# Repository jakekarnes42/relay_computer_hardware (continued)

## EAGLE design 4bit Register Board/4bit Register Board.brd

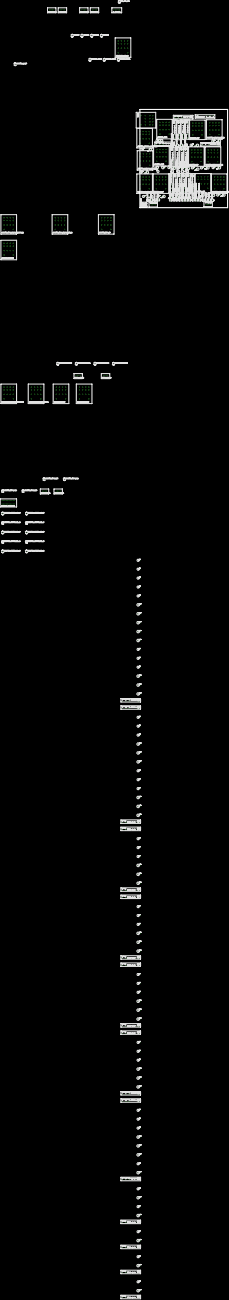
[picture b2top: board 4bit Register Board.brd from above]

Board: 2 copper layers, 125.0 x 140.0 mm, 237 parts (0 on the bottom side), 134 nets, no tracks yet.

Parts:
CCR:D3, CCR:D5, CCR:D7, CCR:D9, CCR:D11, CCR:D13: 1N4007; RAD2,5
CCR:D4, CCR:D6, CCR:D8, CCR:D10, CCR:D12, CCR:D14: 1N5359VERT_SML; RAD2.5_D2
CCR:ENABLE_DATA:D1: 1N4007; RAD2,5
CCR:ENABLE_DATA:D2: 1N5359VERT_SML; RAD2.5_D2
CCR:ENABLE_DATA:K1: PY14-02
CCR:K2: HF41F-12-Z
CCR:K3: PY14-02
CCR:K4, CCR:K5, CCR:K6, CCR:K7: HF41F-12-H
CCR:LED0, CCR:LED1, CCR:LED2, CCR:LED3: LED3MM
CCR_CONTROL:X1: 55932-0530
INPUT_ADDR:X1: 55932-0430
INPUT_AU_CCR:X1: 55932-0430
INPUT_AU_DATA:X1: 55932-0430
INPUT_DATA:X1: 55932-0430
INPUT_LU_CCR:X1: 55932-0430
INPUT_LU_DATA:X1: 55932-0430
LED_ADDR0, LED_ADDR1, LED_ADDR2, LED_ADDR3: LED3MM
LED_DATA0, LED_DATA1, LED_DATA2, LED_DATA3: LED3MM
LED_LOAD_CCR: LED3MM
OUTPUT_AU_TMP1:X1, OUTPUT_AU_TMP2:X1: 55932-0430
OUTPUT_LU_TMP1:X1, OUTPUT_LU_TMP2:X1: 55932-0430
PWR_BLK:PWR: PWR_BLK; 1751248
REGISTER_A:D3, REGISTER_A:D5, REGISTER_A:D7, REGISTER_A:D9, REGISTER_A:D11, REGISTER_A:D13, REGISTER_A:D17, REGISTER_A:D19: 1N4007; RAD2,5
REGISTER_A:D4, REGISTER_A:D6, REGISTER_A:D8, REGISTER_A:D10, REGISTER_A:D12, REGISTER_A:D14, REGISTER_A:D18, REGISTER_A:D20: 1N5359VERT_SML; RAD2.5_D2
REGISTER_A:ENABLE_ADDRESS:D1: 1N4007; RAD2,5
REGISTER_A:ENABLE_ADDRESS:D2: 1N5359VERT_SML; RAD2.5_D2
REGISTER_A:ENABLE_ADDRESS:K1: PY14-02
REGISTER_A:ENABLE_DATA:D1: 1N4007; RAD2,5
REGISTER_A:ENABLE_DATA:D2: 1N5359VERT_SML; RAD2.5_D2
REGISTER_A:ENABLE_DATA:K1: PY14-02
REGISTER_A:K2, REGISTER_A:K9: HF41F-12-Z
REGISTER_A:K3, REGISTER_A:K10: PY14-02
REGISTER_A:K4, REGISTER_A:K5, REGISTER_A:K6, REGISTER_A:K7: HF41F-12-H
REGISTER_A:LED0, REGISTER_A:LED1, REGISTER_A:LED2, REGISTER_A:LED3: LED3MM
REGISTER_B:D3, REGISTER_B:D5, REGISTER_B:D7, REGISTER_B:D9, REGISTER_B:D11, REGISTER_B:D13, REGISTER_B:D17, REGISTER_B:D19: 1N4007; RAD2,5
REGISTER_B:D4, REGISTER_B:D6, REGISTER_B:D8, REGISTER_B:D10, REGISTER_B:D12, REGISTER_B:D14, REGISTER_B:D18, REGISTER_B:D20: 1N5359VERT_SML; RAD2.5_D2
REGISTER_B:ENABLE_ADDRESS:D1: 1N4007; RAD2,5
REGISTER_B:ENABLE_ADDRESS:D2: 1N5359VERT_SML; RAD2.5_D2
REGISTER_B:ENABLE_ADDRESS:K1: PY14-02
REGISTER_B:ENABLE_DATA:D1: 1N4007; RAD2,5
REGISTER_B:ENABLE_DATA:D2: 1N5359VERT_SML; RAD2.5_D2
REGISTER_B:ENABLE_DATA:K1: PY14-02
REGISTER_B:K2, REGISTER_B:K9: HF41F-12-Z
REGISTER_B:K3, REGISTER_B:K10: PY14-02
REGISTER_B:K4, REGISTER_B:K5, REGISTER_B:K6, REGISTER_B:K7: HF41F-12-H
REGISTER_B:LED0, REGISTER_B:LED1, REGISTER_B:LED2, REGISTER_B:LED3: LED3MM
REGISTER_C:D3, REGISTER_C:D5, REGISTER_C:D7, REGISTER_C:D9, REGISTER_C:D11, REGISTER_C:D13, REGISTER_C:D17, REGISTER_C:D19: 1N4007; RAD2,5
REGISTER_C:D4, REGISTER_C:D6, REGISTER_C:D8, REGISTER_C:D10, REGISTER_C:D12, REGISTER_C:D14, REGISTER_C:D18, REGISTER_C:D20: 1N5359VERT_SML; RAD2.5_D2
REGISTER_C:ENABLE_ADDRESS:D1: 1N4007; RAD2,5
REGISTER_C:ENABLE_ADDRESS:D2: 1N5359VERT_SML; RAD2.5_D2
REGISTER_C:ENABLE_ADDRESS:K1: PY14-02
REGISTER_C:ENABLE_DATA:D1: 1N4007; RAD2,5
REGISTER_C:ENABLE_DATA:D2: 1N5359VERT_SML; RAD2.5_D2
REGISTER_C:ENABLE_DATA:K1: PY14-02
REGISTER_C:K2, REGISTER_C:K9: HF41F-12-Z
REGISTER_C:K3, REGISTER_C:K10: PY14-02
REGISTER_C:K4, REGISTER_C:K5, REGISTER_C:K6, REGISTER_C:K7: HF41F-12-H
REGISTER_C:LED0, REGISTER_C:LED1, REGISTER_C:LED2, REGISTER_C:LED3: LED3MM
REGISTER_CONTROL:LED_1, REGISTER_CONTROL:LED_2, REGISTER_CONTROL:LED_3, REGISTER_CONTROL:LED_4, REGISTER_CONTROL:LED_5, REGISTER_CONTROL:LED_6, REGISTER_CONTROL:LED_7, REGISTER_CONTROL:LED_8, REGISTER_CONTROL:LED_9, REGISTER_CONTROL:LED_10, REGISTER_CONTROL:LED_11, REGISTER_CONTROL:LED_12, REGISTER_CONTROL:LED_13, REGISTER_CONTROL:LED_14, REGISTER_CONTROL:LED_15, REGISTER_CONTROL:LED_16, REGISTER_CONTROL:LED_17, REGISTER_CONTROL:LED_18, REGISTER_CONTROL:LED_19, REGISTER_CONTROL:LED_20: LED3MM
REGISTER_CONTROL:X2: 55917-2030
REGISTER_TMP1:D3, REGISTER_TMP1:D5, REGISTER_TMP1:D7, REGISTER_TMP1:D9, REGISTER_TMP1:D11, REGISTER_TMP1:D13, REGISTER_TMP1:D17, REGISTER_TMP1:D19, REGISTER_TMP1:ENABLE_ADDRESS:D1, REGISTER_TMP1:ENABLE_DATA:D1, REGISTER_TMP2:D3, REGISTER_TMP2:D5, REGISTER_TMP2:D7, REGISTER_TMP2:D9, REGISTER_TMP2:D11, REGISTER_TMP2:D13, REGISTER_TMP2:D17, REGISTER_TMP2:D19, REGISTER_TMP2:ENABLE_ADDRESS:D1, REGISTER_TMP2:ENABLE_DATA:D1: 1N4007; RAD2,5
REGISTER_TMP1:D4, REGISTER_TMP1:D6, REGISTER_TMP1:D8, REGISTER_TMP1:D10, REGISTER_TMP1:D12, REGISTER_TMP1:D14, REGISTER_TMP1:D18, REGISTER_TMP1:D20, REGISTER_TMP1:ENABLE_ADDRESS:D2, REGISTER_TMP1:ENABLE_DATA:D2, REGISTER_TMP2:D4, REGISTER_TMP2:D6, REGISTER_TMP2:D8, REGISTER_TMP2:D10, REGISTER_TMP2:D12, REGISTER_TMP2:D14, REGISTER_TMP2:D18, REGISTER_TMP2:D20, REGISTER_TMP2:ENABLE_ADDRESS:D2, REGISTER_TMP2:ENABLE_DATA:D2: 1N5359VERT_SML; RAD2.5_D2
REGISTER_TMP1:ENABLE_ADDRESS:K1, REGISTER_TMP1:ENABLE_DATA:K1, REGISTER_TMP1:K3, REGISTER_TMP1:K10, REGISTER_TMP2:ENABLE_ADDRESS:K1, REGISTER_TMP2:ENABLE_DATA:K1, REGISTER_TMP2:K3, REGISTER_TMP2:K10: PY14-02
REGISTER_TMP1:K2, REGISTER_TMP1:K9, REGISTER_TMP2:K2, REGISTER_TMP2:K9: HF41F-12-Z
REGISTER_TMP1:K4, REGISTER_TMP1:K5, REGISTER_TMP1:K6, REGISTER_TMP1:K7, REGISTER_TMP2:K4, REGISTER_TMP2:K5, REGISTER_TMP2:K6, REGISTER_TMP2:K7: HF41F-12-H
REGISTER_TMP1:LED0, REGISTER_TMP1:LED1, REGISTER_TMP1:LED2, REGISTER_TMP1:LED3, REGISTER_TMP2:LED0, REGISTER_TMP2:LED1, REGISTER_TMP2:LED2, REGISTER_TMP2:LED3: LED3MM

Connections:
+12V: CCR:K2.4, CCR:K3.31, CCR:K3.41, PWR_BLK:PWR.2, REGISTER_A:K2.4, REGISTER_A:K3.31, REGISTER_A:K3.41, REGISTER_A:K9.4, REGISTER_A:K10.31, REGISTER_A:K10.41, REGISTER_B:K2.4, REGISTER_B:K3.31, REGISTER_B:K3.41, REGISTER_B:K9.4, REGISTER_B:K10.31, REGISTER_B:K10.41, REGISTER_C:K2.4, REGISTER_C:K3.31, REGISTER_C:K3.41, REGISTER_C:K9.4, REGISTER_C:K10.31, REGISTER_C:K10.41, REGISTER_TMP1:K2.4, REGISTER_TMP1:K3.31, REGISTER_TMP1:K3.41, REGISTER_TMP1:K9.4, REGISTER_TMP1:K10.31, REGISTER_TMP1:K10.41, REGISTER_TMP2:K2.4, REGISTER_TMP2:K3.31, REGISTER_TMP2:K3.41, REGISTER_TMP2:K9.4, REGISTER_TMP2:K10.31, REGISTER_TMP2:K10.41
ADDR0: INPUT_ADDR:X1.4, LED_ADDR0.A, REGISTER_A:ENABLE_ADDRESS:K1.14, REGISTER_B:ENABLE_ADDRESS:K1.14, REGISTER_C:ENABLE_ADDRESS:K1.14, REGISTER_TMP1:ENABLE_ADDRESS:K1.14, REGISTER_TMP2:ENABLE_ADDRESS:K1.14
ADDR1: INPUT_ADDR:X1.3, LED_ADDR1.A, REGISTER_A:ENABLE_ADDRESS:K1.24, REGISTER_B:ENABLE_ADDRESS:K1.24, REGISTER_C:ENABLE_ADDRESS:K1.24, REGISTER_TMP1:ENABLE_ADDRESS:K1.24, REGISTER_TMP2:ENABLE_ADDRESS:K1.24
ADDR2: INPUT_ADDR:X1.2, LED_ADDR2.A, REGISTER_A:ENABLE_ADDRESS:K1.34, REGISTER_B:ENABLE_ADDRESS:K1.34, REGISTER_C:ENABLE_ADDRESS:K1.34, REGISTER_TMP1:ENABLE_ADDRESS:K1.34, REGISTER_TMP2:ENABLE_ADDRESS:K1.34
ADDR3: INPUT_ADDR:X1.1, LED_ADDR3.A, REGISTER_A:ENABLE_ADDRESS:K1.44, REGISTER_B:ENABLE_ADDRESS:K1.44, REGISTER_C:ENABLE_ADDRESS:K1.44, REGISTER_TMP1:ENABLE_ADDRESS:K1.44, REGISTER_TMP2:ENABLE_ADDRESS:K1.44
CCR:D$2: CCR:D3.A, CCR:D4.A
CCR:D$3: CCR:D5.A, CCR:D6.A
CCR:D$4: CCR:D7.A, CCR:D8.A
CCR:D$5: CCR:D9.A, CCR:D10.A
CCR:D$6: CCR:D11.A, CCR:D12.A
CCR:D$7: CCR:D13.A, CCR:D14.A
CCR:ENABLE_DATA:D$1: CCR:ENABLE_DATA:D1.A, CCR:ENABLE_DATA:D2.A
CCR:HOLD: CCR:K3.32, CCR:K4.5, CCR:K5.5, CCR:K6.5, CCR:K7.5
CCR:IN: CCR:D3.C, CCR:K2.1, CCR:K3.42
CCR:SELECT: CCR:ENABLE_DATA:D1.C, CCR:ENABLE_DATA:K1.A2, CCR:K2.3
DATA0: INPUT_AU_DATA:X1.4, INPUT_DATA:X1.4, INPUT_LU_DATA:X1.4, LED_DATA0.A, REGISTER_A:ENABLE_DATA:K1.44, REGISTER_B:ENABLE_DATA:K1.44, REGISTER_C:ENABLE_DATA:K1.44, REGISTER_TMP1:ENABLE_DATA:K1.44, REGISTER_TMP2:ENABLE_DATA:K1.44
DATA1: INPUT_AU_DATA:X1.3, INPUT_DATA:X1.3, INPUT_LU_DATA:X1.3, LED_DATA1.A, REGISTER_A:ENABLE_DATA:K1.34, REGISTER_B:ENABLE_DATA:K1.34, REGISTER_C:ENABLE_DATA:K1.34, REGISTER_TMP1:ENABLE_DATA:K1.34, REGISTER_TMP2:ENABLE_DATA:K1.34
DATA2: INPUT_AU_DATA:X1.2, INPUT_DATA:X1.2, INPUT_LU_DATA:X1.2, LED_DATA2.A, REGISTER_A:ENABLE_DATA:K1.24, REGISTER_B:ENABLE_DATA:K1.24, REGISTER_C:ENABLE_DATA:K1.24, REGISTER_TMP1:ENABLE_DATA:K1.24, REGISTER_TMP2:ENABLE_DATA:K1.24
DATA3: INPUT_AU_DATA:X1.1, INPUT_DATA:X1.1, INPUT_LU_DATA:X1.1, LED_DATA3.A, REGISTER_A:ENABLE_DATA:K1.14, REGISTER_B:ENABLE_DATA:K1.14, REGISTER_C:ENABLE_DATA:K1.14, REGISTER_TMP1:ENABLE_DATA:K1.14, REGISTER_TMP2:ENABLE_DATA:K1.14
GND: CCR:D4.C, CCR:D6.C, CCR:D8.C, CCR:D10.C, CCR:D12.C, CCR:D14.C, CCR:ENABLE_DATA:D2.C, CCR:ENABLE_DATA:K1.A1, CCR:K2.2, CCR:K3.A1, CCR:K4.2, CCR:K5.2, CCR:K6.2, CCR:K7.2, CCR:LED0.K, CCR:LED1.K, CCR:LED2.K, CCR:LED3.K, LED_ADDR0.K, LED_ADDR1.K, LED_ADDR2.K, LED_ADDR3.K, LED_DATA0.K, LED_DATA1.K, LED_DATA2.K, LED_DATA3.K, LED_LOAD_CCR.K, PWR_BLK:PWR.1, REGISTER_A:D4.C, REGISTER_A:D6.C, REGISTER_A:D8.C, REGISTER_A:D10.C, REGISTER_A:D12.C, REGISTER_A:D14.C, REGISTER_A:D18.C, REGISTER_A:D20.C, REGISTER_A:ENABLE_ADDRESS:D2.C, REGISTER_A:ENABLE_ADDRESS:K1.A1, REGISTER_A:ENABLE_DATA:D2.C, REGISTER_A:ENABLE_DATA:K1.A1, REGISTER_A:K2.2, REGISTER_A:K3.A1, REGISTER_A:K4.2, REGISTER_A:K5.2, REGISTER_A:K6.2, REGISTER_A:K7.2, REGISTER_A:K9.2, REGISTER_A:K10.A1, REGISTER_A:LED0.K, REGISTER_A:LED1.K, REGISTER_A:LED2.K, REGISTER_A:LED3.K, REGISTER_B:D4.C, REGISTER_B:D6.C, REGISTER_B:D8.C, REGISTER_B:D10.C, REGISTER_B:D12.C, REGISTER_B:D14.C, REGISTER_B:D18.C, REGISTER_B:D20.C, REGISTER_B:ENABLE_ADDRESS:D2.C, REGISTER_B:ENABLE_ADDRESS:K1.A1, REGISTER_B:ENABLE_DATA:D2.C, REGISTER_B:ENABLE_DATA:K1.A1, REGISTER_B:K2.2, REGISTER_B:K3.A1, REGISTER_B:K4.2, REGISTER_B:K5.2, REGISTER_B:K6.2, REGISTER_B:K7.2, REGISTER_B:K9.2, REGISTER_B:K10.A1, REGISTER_B:LED0.K, REGISTER_B:LED1.K, REGISTER_B:LED2.K, REGISTER_B:LED3.K, REGISTER_C:D4.C, REGISTER_C:D6.C, REGISTER_C:D8.C, REGISTER_C:D10.C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
LOADA_A: REGISTER_A:D19.C, REGISTER_A:K10.A2, REGISTER_CONTROL:LED_11.A
LOADA_B: REGISTER_B:D19.C, REGISTER_B:K10.A2, REGISTER_CONTROL:LED_13.A
LOADA_C: REGISTER_C:D19.C, REGISTER_C:K10.A2, REGISTER_CONTROL:LED_15.A
LOADA_TMP1: REGISTER_CONTROL:LED_17.A, REGISTER_TMP1:D19.C, REGISTER_TMP1:K10.A2
LOADA_TMP2: REGISTER_CONTROL:LED_19.A, REGISTER_TMP2:D19.C, REGISTER_TMP2:K10.A2
LOADD_A: REGISTER_A:D5.C, REGISTER_A:K3.A2, REGISTER_CONTROL:LED_1.A, REGISTER_CONTROL:X2.1
LOADD_B: REGISTER_B:D5.C, REGISTER_B:K3.A2, REGISTER_CONTROL:LED_3.A, REGISTER_CONTROL:X2.5
LOADD_C: REGISTER_C:D5.C, REGISTER_C:K3.A2, REGISTER_CONTROL:LED_5.A, REGISTER_CONTROL:X2.9
LOADD_TMP1: REGISTER_CONTROL:LED_7.A, REGISTER_CONTROL:X2.13, REGISTER_TMP1:D5.C, REGISTER_TMP1:K3.A2
LOADD_TMP2: REGISTER_CONTROL:LED_9.A, REGISTER_CONTROL:X2.17, REGISTER_TMP2:D5.C, REGISTER_TMP2:K3.A2
LOAD_CCR: CCR:D5.C, CCR:K3.A2, CCR_CONTROL:X1.1, LED_LOAD_CCR.A
unnamed: OUTPUT_AU_TMP2:X1.1, OUTPUT_LU_TMP2:X1.1, REGISTER_TMP2:D7.C, REGISTER_TMP2:ENABLE_ADDRESS:K1.41, REGISTER_TMP2:ENABLE_DATA:K1.11, REGISTER_TMP2:K4.1, REGISTER_TMP2:K4.4, REGISTER_TMP2:LED3.A
unnamed: OUTPUT_AU_TMP2:X1.2, OUTPUT_LU_TMP2:X1.2, REGISTER_TMP2:D9.C, REGISTER_TMP2:ENABLE_ADDRESS:K1.31, REGISTER_TMP2:ENABLE_DATA:K1.21, REGISTER_TMP2:K5.1, REGISTER_TMP2:K5.4, REGISTER_TMP2:LED2.A
unnamed: OUTPUT_AU_TMP2:X1.3, OUTPUT_LU_TMP2:X1.3, REGISTER_TMP2:D11.C, REGISTER_TMP2:ENABLE_ADDRESS:K1.21, REGISTER_TMP2:ENABLE_DATA:K1.31, REGISTER_TMP2:K6.1, REGISTER_TMP2:K6.4, REGISTER_TMP2:LED1.A
unnamed: OUTPUT_AU_TMP2:X1.4, OUTPUT_LU_TMP2:X1.4, REGISTER_TMP2:D13.C, REGISTER_TMP2:ENABLE_ADDRESS:K1.11, REGISTER_TMP2:ENABLE_DATA:K1.41, REGISTER_TMP2:K7.1, REGISTER_TMP2:K7.4, REGISTER_TMP2:LED0.A
unnamed: REGISTER_B:D7.C, REGISTER_B:ENABLE_ADDRESS:K1.41, REGISTER_B:ENABLE_DATA:K1.11, REGISTER_B:K4.1, REGISTER_B:K4.4, REGISTER_B:LED3.A
unnamed: CCR:ENABLE_DATA:K1.14, INPUT_AU_CCR:X1.4, INPUT_LU_CCR:X1.4
unnamed: CCR:ENABLE_DATA:K1.24, INPUT_AU_CCR:X1.3, INPUT_LU_CCR:X1.3
unnamed: CCR:ENABLE_DATA:K1.34, INPUT_AU_CCR:X1.2, INPUT_LU_CCR:X1.2
unnamed: CCR:ENABLE_DATA:K1.44, INPUT_AU_CCR:X1.1, INPUT_LU_CCR:X1.1
unnamed: CCR:D7.C, CCR:ENABLE_DATA:K1.11, CCR:K4.1, CCR:K4.4, CCR:LED3.A, CCR_CONTROL:X1.2
unnamed: CCR:D9.C, CCR:ENABLE_DATA:K1.21, CCR:K5.1, CCR:K5.4, CCR:LED2.A, CCR_CONTROL:X1.3
unnamed: CCR:D11.C, CCR:ENABLE_DATA:K1.31, CCR:K6.1, CCR:K6.4, CCR:LED1.A, CCR_CONTROL:X1.4
unnamed: CCR:D13.C, CCR:ENABLE_DATA:K1.41, CCR:K7.1, CCR:K7.4, CCR:LED0.A, CCR_CONTROL:X1.5
unnamed: OUTPUT_AU_TMP1:X1.1, OUTPUT_LU_TMP1:X1.1, REGISTER_TMP1:D7.C, REGISTER_TMP1:ENABLE_ADDRESS:K1.41, REGISTER_TMP1:ENABLE_DATA:K1.11, REGISTER_TMP1:K4.1, REGISTER_TMP1:K4.4, REGISTER_TMP1:LED3.A
unnamed: OUTPUT_AU_TMP1:X1.2, OUTPUT_LU_TMP1:X1.2, REGISTER_TMP1:D9.C, REGISTER_TMP1:ENABLE_ADDRESS:K1.31, REGISTER_TMP1:ENABLE_DATA:K1.21, REGISTER_TMP1:K5.1, REGISTER_TMP1:K5.4, REGISTER_TMP1:LED2.A
unnamed: OUTPUT_AU_TMP1:X1.3, OUTPUT_LU_TMP1:X1.3, REGISTER_TMP1:D11.C, REGISTER_TMP1:ENABLE_ADDRESS:K1.21, REGISTER_TMP1:ENABLE_DATA:K1.31, REGISTER_TMP1:K6.1, REGISTER_TMP1:K6.4, REGISTER_TMP1:LED1.A
unnamed: OUTPUT_AU_TMP1:X1.4, OUTPUT_LU_TMP1:X1.4, REGISTER_TMP1:D13.C, REGISTER_TMP1:ENABLE_ADDRESS:K1.11, REGISTER_TMP1:ENABLE_DATA:K1.41, REGISTER_TMP1:K7.1, REGISTER_TMP1:K7.4, REGISTER_TMP1:LED0.A
REGISTER_A:D$2: REGISTER_A:D3.A, REGISTER_A:D4.A
REGISTER_A:D$3: REGISTER_A:D5.A, REGISTER_A:D6.A
REGISTER_A:D$4: REGISTER_A:D7.A, REGISTER_A:D8.A
REGISTER_A:D$5: REGISTER_A:D9.A, REGISTER_A:D10.A
REGISTER_A:D$6: REGISTER_A:D11.A, REGISTER_A:D12.A
REGISTER_A:D$7: REGISTER_A:D13.A, REGISTER_A:D14.A
REGISTER_A:D$9: REGISTER_A:D17.A, REGISTER_A:D18.A
REGISTER_A:D$10: REGISTER_A:D19.A, REGISTER_A:D20.A
REGISTER_A:ENABLE_ADDRESS:D$1: REGISTER_A:ENABLE_ADDRESS:D1.A, REGISTER_A:ENABLE_ADDRESS:D2.A
REGISTER_A:ENABLE_DATA:D$1: REGISTER_A:ENABLE_DATA:D1.A, REGISTER_A:ENABLE_DATA:D2.A
REGISTER_A:HOLD: REGISTER_A:K3.32, REGISTER_A:K4.5, REGISTER_A:K5.5, REGISTER_A:K6.5, REGISTER_A:K7.5, REGISTER_A:K10.32
REGISTER_A:IN: REGISTER_A:D3.C, REGISTER_A:K2.1, REGISTER_A:K3.42
REGISTER_A:IN1: REGISTER_A:D17.C, REGISTER_A:K9.1, REGISTER_A:K10.42
REGISTER_A:R0: REGISTER_A:D13.C, REGISTER_A:ENABLE_ADDRESS:K1.11, REGISTER_A:ENABLE_DATA:K1.41, REGISTER_A:K7.1, REGISTER_A:K7.4, REGISTER_A:LED0.A
REGISTER_A:R1: REGISTER_A:D11.C, REGISTER_A:ENABLE_ADDRESS:K1.21, REGISTER_A:ENABLE_DATA:K1.31, REGISTER_A:K6.1, REGISTER_A:K6.4, REGISTER_A:LED1.A
REGISTER_A:R2: REGISTER_A:D9.C, REGISTER_A:ENABLE_ADDRESS:K1.31, REGISTER_A:ENABLE_DATA:K1.21, REGISTER_A:K5.1, REGISTER_A:K5.4, REGISTER_A:LED2.A
REGISTER_A:R3: REGISTER_A:D7.C, REGISTER_A:ENABLE_ADDRESS:K1.41, REGISTER_A:ENABLE_DATA:K1.11, REGISTER_A:K4.1, REGISTER_A:K4.4, REGISTER_A:LED3.A
REGISTER_B:D$2: REGISTER_B:D3.A, REGISTER_B:D4.A
REGISTER_B:D$3: REGISTER_B:D5.A, REGISTER_B:D6.A
REGISTER_B:D$4: REGISTER_B:D7.A, REGISTER_B:D8.A
REGISTER_B:D$5: REGISTER_B:D9.A, REGISTER_B:D10.A
REGISTER_B:D$6: REGISTER_B:D11.A, REGISTER_B:D12.A
REGISTER_B:D$7: REGISTER_B:D13.A, REGISTER_B:D14.A
REGISTER_B:D$9: REGISTER_B:D17.A, REGISTER_B:D18.A
REGISTER_B:D$10: REGISTER_B:D19.A, REGISTER_B:D20.A
REGISTER_B:ENABLE_ADDRESS:D$1: REGISTER_B:ENABLE_ADDRESS:D1.A, REGISTER_B:ENABLE_ADDRESS:D2.A
REGISTER_B:ENABLE_DATA:D$1: REGISTER_B:ENABLE_DATA:D1.A, REGISTER_B:ENABLE_DATA:D2.A
REGISTER_B:HOLD: REGISTER_B:K3.32, REGISTER_B:K4.5, REGISTER_B:K5.5, REGISTER_B:K6.5, REGISTER_B:K7.5, REGISTER_B:K10.32
REGISTER_B:IN: REGISTER_B:D3.C, REGISTER_B:K2.1, REGISTER_B:K3.42
REGISTER_B:IN1: REGISTER_B:D17.C, REGISTER_B:K9.1, REGISTER_B:K10.42
REGISTER_B:R0: REGISTER_B:D13.C, REGISTER_B:ENABLE_ADDRESS:K1.11, REGISTER_B:ENABLE_DATA:K1.41, REGISTER_B:K7.1, REGISTER_B:K7.4, REGISTER_B:LED0.A
REGISTER_B:R1: REGISTER_B:D11.C, REGISTER_B:ENABLE_ADDRESS:K1.21, REGISTER_B:ENABLE_DATA:K1.31, REGISTER_B:K6.1, REGISTER_B:K6.4, REGISTER_B:LED1.A
REGISTER_B:R2: REGISTER_B:D9.C, REGISTER_B:ENABLE_ADDRESS:K1.31, REGISTER_B:ENABLE_DATA:K1.21, REGISTER_B:K5.1, REGISTER_B:K5.4, REGISTER_B:LED2.A
REGISTER_C:D$2: REGISTER_C:D3.A, REGISTER_C:D4.A
REGISTER_C:D$3: REGISTER_C:D5.A, REGISTER_C:D6.A
REGISTER_C:D$4: REGISTER_C:D7.A, REGISTER_C:D8.A
REGISTER_C:D$5: REGISTER_C:D9.A, REGISTER_C:D10.A
REGISTER_C:D$6: REGISTER_C:D11.A, REGISTER_C:D12.A
REGISTER_C:D$7: REGISTER_C:D13.A, REGISTER_C:D14.A
REGISTER_C:D$9: REGISTER_C:D17.A, REGISTER_C:D18.A
REGISTER_C:D$10: REGISTER_C:D19.A, REGISTER_C:D20.A
REGISTER_C:ENABLE_ADDRESS:D$1: REGISTER_C:ENABLE_ADDRESS:D1.A, REGISTER_C:ENABLE_ADDRESS:D2.A
REGISTER_C:ENABLE_DATA:D$1: REGISTER_C:ENABLE_DATA:D1.A, REGISTER_C:ENABLE_DATA:D2.A
REGISTER_C:HOLD: REGISTER_C:K3.32, REGISTER_C:K4.5, REGISTER_C:K5.5, REGISTER_C:K6.5, REGISTER_C:K7.5, REGISTER_C:K10.32
REGISTER_C:IN: REGISTER_C:D3.C, REGISTER_C:K2.1, REGISTER_C:K3.42
REGISTER_C:IN1: REGISTER_C:D17.C, REGISTER_C:K9.1, REGISTER_C:K10.42
REGISTER_C:R0: REGISTER_C:D13.C, REGISTER_C:ENABLE_ADDRESS:K1.11, REGISTER_C:ENABLE_DATA:K1.41, REGISTER_C:K7.1, REGISTER_C:K7.4, REGISTER_C:LED0.A
REGISTER_C:R1: REGISTER_C:D11.C, REGISTER_C:ENABLE_ADDRESS:K1.21, REGISTER_C:ENABLE_DATA:K1.31, REGISTER_C:K6.1, REGISTER_C:K6.4, REGISTER_C:LED1.A
REGISTER_C:R2: REGISTER_C:D9.C, REGISTER_C:ENABLE_ADDRESS:K1.31, REGISTER_C:ENABLE_DATA:K1.21, REGISTER_C:K5.1, REGISTER_C:K5.4, REGISTER_C:LED2.A
REGISTER_C:R3: REGISTER_C:D7.C, REGISTER_C:ENABLE_ADDRESS:K1.41, REGISTER_C:ENABLE_DATA:K1.11, REGISTER_C:K4.1, REGISTER_C:K4.4, REGISTER_C:LED3.A
REGISTER_TMP1:D$2: REGISTER_TMP1:D3.A, REGISTER_TMP1:D4.A
REGISTER_TMP1:D$3: REGISTER_TMP1:D5.A, REGISTER_TMP1:D6.A
REGISTER_TMP1:D$4: REGISTER_TMP1:D7.A, REGISTER_TMP1:D8.A
REGISTER_TMP1:D$5: REGISTER_TMP1:D9.A, REGISTER_TMP1:D10.A
REGISTER_TMP1:D$6: REGISTER_TMP1:D11.A, REGISTER_TMP1:D12.A
REGISTER_TMP1:D$7: REGISTER_TMP1:D13.A, REGISTER_TMP1:D14.A
REGISTER_TMP1:D$9: REGISTER_TMP1:D17.A, REGISTER_TMP1:D18.A
REGISTER_TMP1:D$10: REGISTER_TMP1:D19.A, REGISTER_TMP1:D20.A
REGISTER_TMP1:ENABLE_ADDRESS:D$1: REGISTER_TMP1:ENABLE_ADDRESS:D1.A, REGISTER_TMP1:ENABLE_ADDRESS:D2.A
REGISTER_TMP1:ENABLE_DATA:D$1: REGISTER_TMP1:ENABLE_DATA:D1.A, REGISTER_TMP1:ENABLE_DATA:D2.A
REGISTER_TMP1:HOLD: REGISTER_TMP1:K3.32, REGISTER_TMP1:K4.5, REGISTER_TMP1:K5.5, REGISTER_TMP1:K6.5, REGISTER_TMP1:K7.5, REGISTER_TMP1:K10.32
REGISTER_TMP1:IN: REGISTER_TMP1:D3.C, REGISTER_TMP1:K2.1, REGISTER_TMP1:K3.42
REGISTER_TMP1:IN1: REGISTER_TMP1:D17.C, REGISTER_TMP1:K9.1, REGISTER_TMP1:K10.42
REGISTER_TMP2:D$2: REGISTER_TMP2:D3.A, REGISTER_TMP2:D4.A
REGISTER_TMP2:D$3: REGISTER_TMP2:D5.A, REGISTER_TMP2:D6.A
REGISTER_TMP2:D$4: REGISTER_TMP2:D7.A, REGISTER_TMP2:D8.A
REGISTER_TMP2:D$5: REGISTER_TMP2:D9.A, REGISTER_TMP2:D10.A
REGISTER_TMP2:D$6: REGISTER_TMP2:D11.A, REGISTER_TMP2:D12.A
REGISTER_TMP2:D$7: REGISTER_TMP2:D13.A, REGISTER_TMP2:D14.A
REGISTER_TMP2:D$9: REGISTER_TMP2:D17.A, REGISTER_TMP2:D18.A
REGISTER_TMP2:D$10: REGISTER_TMP2:D19.A, REGISTER_TMP2:D20.A
REGISTER_TMP2:ENABLE_ADDRESS:D$1: REGISTER_TMP2:ENABLE_ADDRESS:D1.A, REGISTER_TMP2:ENABLE_ADDRESS:D2.A
REGISTER_TMP2:ENABLE_DATA:D$1: REGISTER_TMP2:ENABLE_DATA:D1.A, REGISTER_TMP2:ENABLE_DATA:D2.A
REGISTER_TMP2:HOLD: REGISTER_TMP2:K3.32, REGISTER_TMP2:K4.5, REGISTER_TMP2:K5.5, REGISTER_TMP2:K6.5, REGISTER_TMP2:K7.5, REGISTER_TMP2:K10.32
REGISTER_TMP2:IN: REGISTER_TMP2:D3.C, REGISTER_TMP2:K2.1, REGISTER_TMP2:K3.42
REGISTER_TMP2:IN1: REGISTER_TMP2:D17.C, REGISTER_TMP2:K9.1, REGISTER_TMP2:K10.42
SELECTA_A: REGISTER_A:ENABLE_ADDRESS:D1.C, REGISTER_A:ENABLE_ADDRESS:K1.A2, REGISTER_A:K9.3, REGISTER_CONTROL:LED_12.A
SELECTA_B: REGISTER_B:ENABLE_ADDRESS:D1.C, REGISTER_B:ENABLE_ADDRESS:K1.A2, REGISTER_B:K9.3, REGISTER_CONTROL:LED_14.A
SELECTA_C: REGISTER_C:ENABLE_ADDRESS:D1.C, REGISTER_C:ENABLE_ADDRESS:K1.A2, REGISTER_C:K9.3, REGISTER_CONTROL:LED_16.A
SELECTA_TMP1: REGISTER_CONTROL:LED_18.A, REGISTER_TMP1:ENABLE_ADDRESS:D1.C, REGISTER_TMP1:ENABLE_ADDRESS:K1.A2, REGISTER_TMP1:K9.3
SELECTA_TMP2: REGISTER_CONTROL:LED_20.A, REGISTER_TMP2:ENABLE_ADDRESS:D1.C, REGISTER_TMP2:ENABLE_ADDRESS:K1.A2, REGISTER_TMP2:K9.3
SELECTD_A: REGISTER_A:ENABLE_DATA:D1.C, REGISTER_A:ENABLE_DATA:K1.A2, REGISTER_A:K2.3, REGISTER_CONTROL:LED_2.A, REGISTER_CONTROL:X2.3
SELECTD_B: REGISTER_B:ENABLE_DATA:D1.C, REGISTER_B:ENABLE_DATA:K1.A2, REGISTER_B:K2.3, REGISTER_CONTROL:LED_4.A, REGISTER_CONTROL:X2.7
SELECTD_C: REGISTER_C:ENABLE_DATA:D1.C, REGISTER_C:ENABLE_DATA:K1.A2, REGISTER_C:K2.3, REGISTER_CONTROL:LED_6.A, REGISTER_CONTROL:X2.11
SELECTD_TMP1: REGISTER_CONTROL:LED_8.A, REGISTER_CONTROL:X2.15, REGISTER_TMP1:ENABLE_DATA:D1.C, REGISTER_TMP1:ENABLE_DATA:K1.A2, REGISTER_TMP1:K2.3
SELECTD_TMP2: REGISTER_CONTROL:LED_10.A, REGISTER_CONTROL:X2.19, REGISTER_TMP2:ENABLE_DATA:D1.C, REGISTER_TMP2:ENABLE_DATA:K1.A2, REGISTER_TMP2:K2.3

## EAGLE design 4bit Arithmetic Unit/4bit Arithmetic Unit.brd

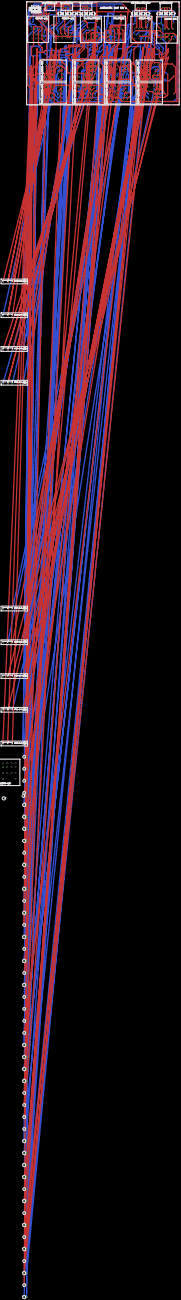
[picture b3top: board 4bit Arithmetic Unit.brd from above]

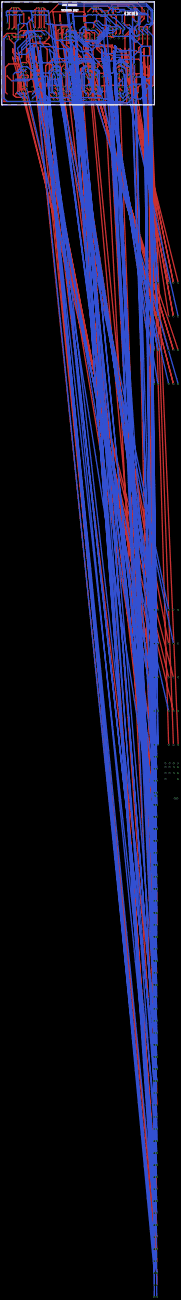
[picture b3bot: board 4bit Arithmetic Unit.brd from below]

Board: 2 copper layers, 97 parts (3 on the bottom side), 114 nets.

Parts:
ADDER8-1:ADDER1-0:D1, ADDER8-1:ADDER1-0:D3, ADDER8-1:ADDER1-1:D1, ADDER8-1:ADDER1-1:D3, ADDER8-1:ADDER1-2:D1, ADDER8-1:ADDER1-2:D3, ADDER8-1:ADDER1-3:D1, ADDER8-1:ADDER1-3:D3, ADDER8-1:D1, ADDER8-1:D3: 1N4007; RAD2,5
ADDER8-1:ADDER1-0:D2, ADDER8-1:ADDER1-0:D4, ADDER8-1:ADDER1-1:D2, ADDER8-1:ADDER1-1:D4, ADDER8-1:ADDER1-2:D2, ADDER8-1:ADDER1-2:D4, ADDER8-1:ADDER1-3:D2, ADDER8-1:ADDER1-3:D4, ADDER8-1:D2, ADDER8-1:D4: 1N5359VERT_SML; RAD2.5_D2
ADDER8-1:ADDER1-0:K1, ADDER8-1:ADDER1-0:K2, ADDER8-1:ADDER1-1:K1, ADDER8-1:ADDER1-1:K2, ADDER8-1:ADDER1-2:K1, ADDER8-1:ADDER1-2:K2, ADDER8-1:ADDER1-3:K1, ADDER8-1:ADDER1-3:K2, ADDER8-1:K2: PY14-02
ADDER8-1:K1: HF41F-12-Z
ENABLE4-1:D1, ENABLE4-2:D1, ENABLE4-3:D1, ENABLE4-4:D1: 1N4007; RAD2,5
ENABLE4-1:D2, ENABLE4-2:D2, ENABLE4-3:D2, ENABLE4-4:D2: 1N5359VERT_SML; RAD2.5_D2
ENABLE4-1:K1, ENABLE4-2:K1, ENABLE4-3:K1, ENABLE4-4:K1: PY14-02
INC/DEC_FILTER1:D1: 1N4007; RAD2,5
INC/DEC_FILTER1:D2: 1N5359VERT_SML; RAD2.5_D2
INC/DEC_FILTER1:K1: PY14-02
INPUT3-1:LED0, INPUT3-1:LED1, INPUT3-1:LED2, INPUT4-1:LED0, INPUT4-1:LED1, INPUT4-1:LED2, INPUT4-1:LED3, INPUT4-2:LED0, INPUT4-2:LED1, INPUT4-2:LED2, INPUT4-2:LED3: LED3MM
INPUT3-1:X1: 55932-0330
INPUT4-1:X1, INPUT4-2:X1: 55932-0430
OUTPUT4-1:LED0, OUTPUT4-1:LED1, OUTPUT4-1:LED2, OUTPUT4-1:LED3, OUTPUT4-2:LED0, OUTPUT4-2:LED1, OUTPUT4-2:LED2, OUTPUT4-2:LED3: LED3MM
OUTPUT4-1:X1, OUTPUT4-2:X1: 55932-0430
PWR_BLK:PWR: PWR_BLK; 1751248
SUB_XOR1:D1, SUB_XOR1:D3, SUB_XOR1:D5, SUB_XOR1:D7, SUB_XOR1:D9: 1N4007; RAD2,5
SUB_XOR1:D2, SUB_XOR1:D4, SUB_XOR1:D6, SUB_XOR1:D8, SUB_XOR1:D10: 1N5359VERT_SML; RAD2.5_D2
SUB_XOR1:K1: PY14-02
SUB_XOR1:K2, SUB_XOR1:K3, SUB_XOR1:K4, SUB_XOR1:K5: HF41F-12-Z
ZERO_DETECT1:D1, ZERO_DETECT1:D3, ZERO_DETECT1:D5, ZERO_DETECT1:D7: 1N4007; RAD2,5
ZERO_DETECT1:D2, ZERO_DETECT1:D4, ZERO_DETECT1:D6, ZERO_DETECT1:D8: 1N5359VERT_SML; RAD2.5_D2
ZERO_DETECT1:K1, ZERO_DETECT1:K2, ZERO_DETECT1:K3, ZERO_DETECT1:K4: HF41F-12-Z

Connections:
+12V: ADDER8-1:ADDER1-0:K1.31, ADDER8-1:ADDER1-1:K1.31, ADDER8-1:ADDER1-2:K1.31, ADDER8-1:ADDER1-3:K1.31, ADDER8-1:K1.4, INC/DEC_FILTER1:K1.44, PWR_BLK:PWR.2, SUB_XOR1:K2.4, SUB_XOR1:K3.4, SUB_XOR1:K4.4, SUB_XOR1:K5.4
ADDER8-1:ADDER1-0:D$1: ADDER8-1:ADDER1-0:D1.A, ADDER8-1:ADDER1-0:D2.A
ADDER8-1:ADDER1-0:D$2: ADDER8-1:ADDER1-0:D3.A, ADDER8-1:ADDER1-0:D4.A
ADDER8-1:ADDER1-0:N$1: ADDER8-1:ADDER1-0:K1.12, ADDER8-1:ADDER1-0:K2.44
ADDER8-1:ADDER1-0:N$2: ADDER8-1:ADDER1-0:K1.14, ADDER8-1:ADDER1-0:K1.32, ADDER8-1:ADDER1-0:K2.42
ADDER8-1:ADDER1-0:N$3: ADDER8-1:ADDER1-0:K1.22, ADDER8-1:ADDER1-0:K2.22, ADDER8-1:ADDER1-0:K2.34
ADDER8-1:ADDER1-0:N$4: ADDER8-1:ADDER1-0:K1.24, ADDER8-1:ADDER1-0:K2.24, ADDER8-1:ADDER1-0:K2.32
ADDER8-1:ADDER1-0:N$5: ADDER8-1:ADDER1-0:K1.44, ADDER8-1:ADDER1-0:K2.12
ADDER8-1:ADDER1-0:N$6: ADDER8-1:ADDER1-0:K1.34, ADDER8-1:ADDER1-0:K1.42, ADDER8-1:ADDER1-0:K2.14
ADDER8-1:ADDER1-1:D$1: ADDER8-1:ADDER1-1:D1.A, ADDER8-1:ADDER1-1:D2.A
ADDER8-1:ADDER1-1:D$2: ADDER8-1:ADDER1-1:D3.A, ADDER8-1:ADDER1-1:D4.A
ADDER8-1:ADDER1-1:N$1: ADDER8-1:ADDER1-1:K1.12, ADDER8-1:ADDER1-1:K2.44
ADDER8-1:ADDER1-1:N$2: ADDER8-1:ADDER1-1:K1.14, ADDER8-1:ADDER1-1:K1.32, ADDER8-1:ADDER1-1:K2.42
ADDER8-1:ADDER1-1:N$3: ADDER8-1:ADDER1-1:K1.22, ADDER8-1:ADDER1-1:K2.22, ADDER8-1:ADDER1-1:K2.34
ADDER8-1:ADDER1-1:N$4: ADDER8-1:ADDER1-1:K1.24, ADDER8-1:ADDER1-1:K2.24, ADDER8-1:ADDER1-1:K2.32
ADDER8-1:ADDER1-1:N$5: ADDER8-1:ADDER1-1:K1.44, ADDER8-1:ADDER1-1:K2.12
ADDER8-1:ADDER1-1:N$6: ADDER8-1:ADDER1-1:K1.34, ADDER8-1:ADDER1-1:K1.42, ADDER8-1:ADDER1-1:K2.14
ADDER8-1:ADDER1-2:D$1: ADDER8-1:ADDER1-2:D1.A, ADDER8-1:ADDER1-2:D2.A
ADDER8-1:ADDER1-2:D$2: ADDER8-1:ADDER1-2:D3.A, ADDER8-1:ADDER1-2:D4.A
ADDER8-1:ADDER1-2:N$1: ADDER8-1:ADDER1-2:K1.12, ADDER8-1:ADDER1-2:K2.44
ADDER8-1:ADDER1-2:N$2: ADDER8-1:ADDER1-2:K1.14, ADDER8-1:ADDER1-2:K1.32, ADDER8-1:ADDER1-2:K2.42
ADDER8-1:ADDER1-2:N$3: ADDER8-1:ADDER1-2:K1.22, ADDER8-1:ADDER1-2:K2.22, ADDER8-1:ADDER1-2:K2.34
ADDER8-1:ADDER1-2:N$4: ADDER8-1:ADDER1-2:K1.24, ADDER8-1:ADDER1-2:K2.24, ADDER8-1:ADDER1-2:K2.32
ADDER8-1:ADDER1-2:N$5: ADDER8-1:ADDER1-2:K1.44, ADDER8-1:ADDER1-2:K2.12
ADDER8-1:ADDER1-2:N$6: ADDER8-1:ADDER1-2:K1.34, ADDER8-1:ADDER1-2:K1.42, ADDER8-1:ADDER1-2:K2.14
ADDER8-1:ADDER1-3:D$1: ADDER8-1:ADDER1-3:D1.A, ADDER8-1:ADDER1-3:D2.A
ADDER8-1:ADDER1-3:D$2: ADDER8-1:ADDER1-3:D3.A, ADDER8-1:ADDER1-3:D4.A
ADDER8-1:ADDER1-3:N$1: ADDER8-1:ADDER1-3:K1.12, ADDER8-1:ADDER1-3:K2.44
ADDER8-1:ADDER1-3:N$2: ADDER8-1:ADDER1-3:K1.14, ADDER8-1:ADDER1-3:K1.32, ADDER8-1:ADDER1-3:K2.42
ADDER8-1:ADDER1-3:N$3: ADDER8-1:ADDER1-3:K1.22, ADDER8-1:ADDER1-3:K2.22, ADDER8-1:ADDER1-3:K2.34
ADDER8-1:ADDER1-3:N$4: ADDER8-1:ADDER1-3:K1.24, ADDER8-1:ADDER1-3:K2.24, ADDER8-1:ADDER1-3:K2.32
ADDER8-1:ADDER1-3:N$5: ADDER8-1:ADDER1-3:K1.44, ADDER8-1:ADDER1-3:K2.12
ADDER8-1:ADDER1-3:N$6: ADDER8-1:ADDER1-3:K1.34, ADDER8-1:ADDER1-3:K1.42, ADDER8-1:ADDER1-3:K2.14
ADDER8-1:D$1: ADDER8-1:D1.A, ADDER8-1:D2.A
ADDER8-1:D$2: ADDER8-1:D3.A, ADDER8-1:D4.A
ADDER8-1:IN: ADDER8-1:D3.C, ADDER8-1:K2.A2
ADDER8-1:IN1: ADDER8-1:ADDER1-2:K2.11, ADDER8-1:ADDER1-3:K1.41, ADDER8-1:ADDER1-3:K2.21, ADDER8-1:K2.42
ADDER8-1:N$1: ADDER8-1:ADDER1-0:K2.11, ADDER8-1:ADDER1-1:K1.41, ADDER8-1:ADDER1-1:K2.21
ADDER8-1:N$2: ADDER8-1:ADDER1-0:K2.41, ADDER8-1:ADDER1-1:K1.11, ADDER8-1:ADDER1-1:K2.31
ADDER8-1:N$3: ADDER8-1:ADDER1-1:K2.11, ADDER8-1:ADDER1-2:K1.41, ADDER8-1:ADDER1-2:K2.21
ADDER8-1:N$4: ADDER8-1:ADDER1-1:K2.41, ADDER8-1:ADDER1-2:K1.11, ADDER8-1:ADDER1-2:K2.31
ADDER8-1:N$6: ADDER8-1:ADDER1-2:K2.41, ADDER8-1:ADDER1-3:K1.11, ADDER8-1:ADDER1-3:K2.31, ADDER8-1:K2.44
ADDER8-1:N$7: ADDER8-1:ADDER1-0:K1.11, ADDER8-1:ADDER1-0:K2.31, ADDER8-1:K1.3, ADDER8-1:K2.34
ADDER8-1:N$9: ADDER8-1:ADDER1-0:K1.41, ADDER8-1:ADDER1-0:K2.21, ADDER8-1:K1.5, ADDER8-1:K2.32
AUE: ENABLE4-1:D1.C, ENABLE4-1:K1.A2, ENABLE4-2:D1.C, ENABLE4-2:K1.A2, ENABLE4-3:D1.C, ENABLE4-3:K1.A2, ENABLE4-4:D1.C, ENABLE4-4:K1.A2, INPUT3-1:LED2.A, INPUT3-1:X1.1
CARRY: ENABLE4-3:K1.11, OUTPUT4-2:LED3.A, OUTPUT4-2:X1.1
ENABLE4-1:D$1: ENABLE4-1:D1.A, ENABLE4-1:D2.A
ENABLE4-2:D$1: ENABLE4-2:D1.A, ENABLE4-2:D2.A
ENABLE4-3:D$1: ENABLE4-3:D1.A, ENABLE4-3:D2.A
ENABLE4-4:D$1: ENABLE4-4:D1.A, ENABLE4-4:D2.A
GND: ADDER8-1:ADDER1-0:D2.C, ADDER8-1:ADDER1-0:D4.C, ADDER8-1:ADDER1-0:K1.A1, ADDER8-1:ADDER1-0:K2.A1, ADDER8-1:ADDER1-1:D2.C, ADDER8-1:ADDER1-1:D4.C, ADDER8-1:ADDER1-1:K1.A1, ADDER8-1:ADDER1-1:K2.A1, ADDER8-1:ADDER1-2:D2.C, ADDER8-1:ADDER1-2:D4.C, ADDER8-1:ADDER1-2:K1.A1, ADDER8-1:ADDER1-2:K2.A1, ADDER8-1:ADDER1-3:D2.C, ADDER8-1:ADDER1-3:D4.C, ADDER8-1:ADDER1-3:K1.A1, ADDER8-1:ADDER1-3:K2.A1, ADDER8-1:D2.C, ADDER8-1:D4.C, ADDER8-1:K1.2, ADDER8-1:K2.A1, ENABLE4-1:D2.C, ENABLE4-1:K1.A1, ENABLE4-2:D2.C, ENABLE4-2:K1.A1, ENABLE4-3:D2.C, ENABLE4-3:K1.A1, ENABLE4-4:D2.C, ENABLE4-4:K1.A1, INC/DEC_FILTER1:D2.C, INC/DEC_FILTER1:K1.A1, INPUT3-1:LED0.K, INPUT3-1:LED1.K, INPUT3-1:LED2.K, INPUT4-1:LED0.K, INPUT4-1:LED1.K, INPUT4-1:LED2.K, INPUT4-1:LED3.K, INPUT4-2:LED0.K, INPUT4-2:LED1.K, INPUT4-2:LED2.K, INPUT4-2:LED3.K, OUTPUT4-1:LED0.K, OUTPUT4-1:LED1.K, OUTPUT4-1:LED2.K, OUTPUT4-1:LED3.K, OUTPUT4-2:LED0.K, OUTPUT4-2:LED1.K, OUTPUT4-2:LED2.K, OUTPUT4-2:LED3.K, PWR_BLK:PWR.1, SUB_XOR1:D2.C, SUB_XOR1:D4.C, SUB_XOR1:D6.C, SUB_XOR1:D8.C, SUB_XOR1:D10.C, SUB_XOR1:K1.A1, SUB_XOR1:K2.2, SUB_XOR1:K3.2, SUB_XOR1:K4.2, SUB_XOR1:K5.2
INC/DEC: INC/DEC_FILTER1:D1.C, INC/DEC_FILTER1:K1.A2, INPUT3-1:LED0.A, INPUT3-1:X1.3
INC/DEC_FILTER1:D$1: INC/DEC_FILTER1:D1.A, INC/DEC_FILTER1:D2.A
INPUT3-1:IN1: INPUT3-1:LED1.A, INPUT3-1:X1.2
unnamed: ENABLE4-1:K1.44, INPUT4-1:LED0.A, INPUT4-1:X1.4
unnamed: ENABLE4-1:K1.34, INPUT4-1:LED1.A, INPUT4-1:X1.3
unnamed: ENABLE4-1:K1.24, INPUT4-1:LED2.A, INPUT4-1:X1.2
unnamed: ENABLE4-1:K1.14, INPUT4-1:LED3.A, INPUT4-1:X1.1
unnamed: ENABLE4-2:K1.44, INPUT4-2:LED0.A, INPUT4-2:X1.4
unnamed: ENABLE4-2:K1.34, INPUT4-2:LED1.A, INPUT4-2:X1.3
unnamed: ENABLE4-2:K1.24, INPUT4-2:LED2.A, INPUT4-2:X1.2
unnamed: ENABLE4-2:K1.14, INPUT4-2:LED3.A, INPUT4-2:X1.1
unnamed: ENABLE4-2:K1.11, INC/DEC_FILTER1:K1.12
unnamed: ENABLE4-2:K1.21, INC/DEC_FILTER1:K1.22
unnamed: ENABLE4-2:K1.31, INC/DEC_FILTER1:K1.32
unnamed: ENABLE4-2:K1.41, INC/DEC_FILTER1:K1.42
unnamed: ADDER8-1:ADDER1-0:D3.C, ADDER8-1:ADDER1-0:K2.A2, ENABLE4-1:K1.41
unnamed: ADDER8-1:ADDER1-1:D3.C, ADDER8-1:ADDER1-1:K2.A2, ENABLE4-1:K1.31
unnamed: ADDER8-1:ADDER1-2:D3.C, ADDER8-1:ADDER1-2:K2.A2, ENABLE4-1:K1.21
unnamed: ADDER8-1:ADDER1-3:D3.C, ADDER8-1:ADDER1-3:K2.A2, ENABLE4-1:K1.11
unnamed: INC/DEC_FILTER1:K1.41, SUB_XOR1:D9.C, SUB_XOR1:K5.1
unnamed: INC/DEC_FILTER1:K1.31, SUB_XOR1:D7.C, SUB_XOR1:K4.1
unnamed: INC/DEC_FILTER1:K1.21, SUB_XOR1:D5.C, SUB_XOR1:K3.1
unnamed: INC/DEC_FILTER1:K1.11, SUB_XOR1:D3.C, SUB_XOR1:K2.1
unnamed: ADDER8-1:ADDER1-3:D1.C, ADDER8-1:ADDER1-3:K1.A2, SUB_XOR1:K1.11
unnamed: ADDER8-1:ADDER1-2:D1.C, ADDER8-1:ADDER1-2:K1.A2, SUB_XOR1:K1.21
unnamed: ADDER8-1:ADDER1-1:D1.C, ADDER8-1:ADDER1-1:K1.A2, SUB_XOR1:K1.31
unnamed: ADDER8-1:ADDER1-0:D1.C, ADDER8-1:ADDER1-0:K1.A2, SUB_XOR1:K1.41
unnamed: ADDER8-1:K2.31, ENABLE4-3:K1.14
unnamed: ENABLE4-3:K1.44, ZERO_DETECT1:K4.3
unnamed: ADDER8-1:ADDER1-0:K1.21, ENABLE4-4:K1.44, ZERO_DETECT1:D7.C, ZERO_DETECT1:K4.1
unnamed: ADDER8-1:ADDER1-1:K1.21, ENABLE4-4:K1.34, ZERO_DETECT1:D5.C, ZERO_DETECT1:K3.1
unnamed: ADDER8-1:ADDER1-2:K1.21, ENABLE4-4:K1.24, ZERO_DETECT1:D3.C, ZERO_DETECT1:K2.1
unnamed: ADDER8-1:ADDER1-3:K1.21, ENABLE4-3:K1.34, ENABLE4-4:K1.14, ZERO_DETECT1:D1.C, ZERO_DETECT1:K1.1
unnamed: ADDER8-1:K2.41, ENABLE4-3:K1.24
OVERFLOW: ENABLE4-3:K1.21, OUTPUT4-2:LED2.A, OUTPUT4-2:X1.2
R0: ENABLE4-4:K1.41, OUTPUT4-1:LED0.A, OUTPUT4-1:X1.4
R1: ENABLE4-4:K1.31, OUTPUT4-1:LED1.A, OUTPUT4-1:X1.3
R2: ENABLE4-4:K1.21, OUTPUT4-1:LED2.A, OUTPUT4-1:X1.2
R3: ENABLE4-4:K1.11, OUTPUT4-1:LED3.A, OUTPUT4-1:X1.1
SIGN: ENABLE4-3:K1.31, OUTPUT4-2:LED1.A, OUTPUT4-2:X1.3
SUB: ADDER8-1:D1.C, ADDER8-1:K1.1, SUB_XOR1:D1.C, SUB_XOR1:K1.A2
SUB_XOR1:D$1: SUB_XOR1:D1.A, SUB_XOR1:D2.A
SUB_XOR1:D$2: SUB_XOR1:D3.A, SUB_XOR1:D4.A
SUB_XOR1:D$3: SUB_XOR1:D5.A, SUB_XOR1:D6.A
SUB_XOR1:D$4: SUB_XOR1:D7.A, SUB_XOR1:D8.A
SUB_XOR1:D$5: SUB_XOR1:D9.A, SUB_XOR1:D10.A
SUB_XOR1:N$1: SUB_XOR1:K1.42, SUB_XOR1:K5.5
SUB_XOR1:N$2: SUB_XOR1:K1.44, SUB_XOR1:K5.3
SUB_XOR1:N$3: SUB_XOR1:K1.34, SUB_XOR1:K4.3
SUB_XOR1:N$4: SUB_XOR1:K1.32, SUB_XOR1:K4.5
SUB_XOR1:N$5: SUB_XOR1:K1.24, SUB_XOR1:K3.3
SUB_XOR1:N$6: SUB_XOR1:K1.22, SUB_XOR1:K3.5
SUB_XOR1:N$7: SUB_XOR1:K1.14, SUB_XOR1:K2.3
SUB_XOR1:N$8: SUB_XOR1:K1.12, SUB_XOR1:K2.5
ZERO: ENABLE4-3:K1.41, OUTPUT4-2:LED0.A, OUTPUT4-2:X1.4
ZERO_DETECT1:D$1: ZERO_DETECT1:D1.A, ZERO_DETECT1:D2.A
ZERO_DETECT1:D$2: ZERO_DETECT1:D3.A, ZERO_DETECT1:D4.A
ZERO_DETECT1:D$3: ZERO_DETECT1:D5.A, ZERO_DETECT1:D6.A
ZERO_DETECT1:D$4: ZERO_DETECT1:D7.A, ZERO_DETECT1:D8.A
ZERO_DETECT1:GND: ZERO_DETECT1:D2.C, ZERO_DETECT1:D4.C, ZERO_DETECT1:D6.C, ZERO_DETECT1:D8.C, ZERO_DETECT1:K1.2, ZERO_DETECT1:K2.2, ZERO_DETECT1:K3.2, ZERO_DETECT1:K4.2
ZERO_DETECT1:N$2: ZERO_DETECT1:K1.3, ZERO_DETECT1:K2.4
ZERO_DETECT1:N$3: ZERO_DETECT1:K2.3, ZERO_DETECT1:K3.4
ZERO_DETECT1:N$4: ZERO_DETECT1:K3.3, ZERO_DETECT1:K4.4

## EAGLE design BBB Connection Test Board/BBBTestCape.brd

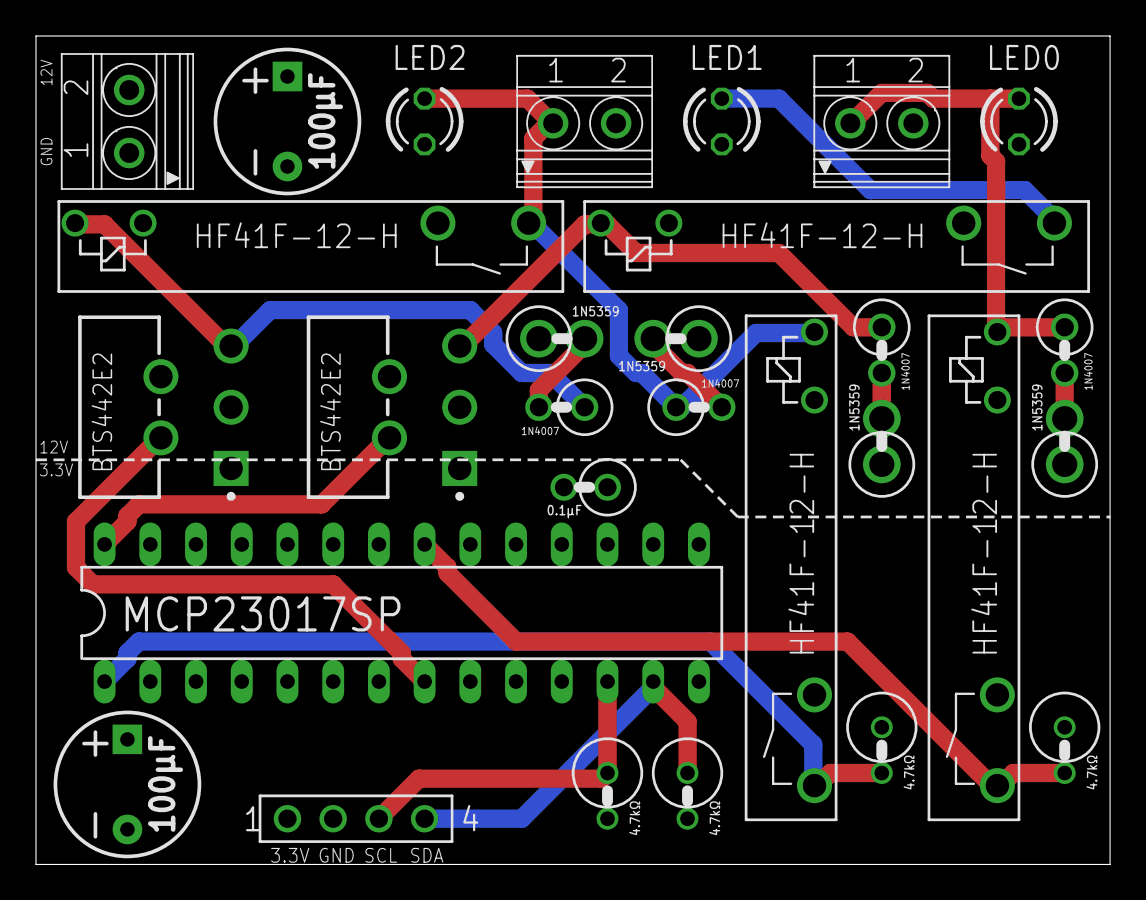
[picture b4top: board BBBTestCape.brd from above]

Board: 4 copper layers, 59.7 x 46.0 mm, 29 parts (0 on the bottom side), 19 nets.

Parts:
3V3_TO_12_1BIT1:D3, 12V_TO_3V3_1BIT1:D5: 1N4007; RAD2,5
3V3_TO_12_1BIT1:D4, 12V_TO_3V3_1BIT1:D6: 1N5359VERT_SML; RAD2.5_D2
3V3_TO_12_1BIT1:K2, 12V_TO_3V3_1BIT1:K3: HF41F-12-H
3V3_TO_12_1BIT1:U1: BTS442E2; TO170P440X1000X1975-5B
12V_PWR_BLK:C1: 100uF; CPOL-RADIAL-5MM-8MM
12V_PWR_BLK:PWR: PWR_BLK; 1751248
BBB_IO1:C1: 100uF; CPOL-RADIAL-5MM-8MM
BBB_IO1:C2: 0.1UF; VERT_CAP
BBB_IO1:IC1: MCP23017SP; DIL28-3
BBB_IO1:R1, BBB_IO1:R2, BBB_IO1:R3, BBB_IO1:R4: 4.7KOHM; RAD2.5_RES
BBB_IO1:SV1: FE04-1
DUAL_12V⇆3V3_1BIT1:3V3_TO_12_1BIT1:D3, DUAL_12V⇆3V3_1BIT1:12V_TO_3V3_1BIT1:D5: 1N4007; RAD2,5
DUAL_12V⇆3V3_1BIT1:3V3_TO_12_1BIT1:D4, DUAL_12V⇆3V3_1BIT1:12V_TO_3V3_1BIT1:D6: 1N5359VERT_SML; RAD2.5_D2
DUAL_12V⇆3V3_1BIT1:3V3_TO_12_1BIT1:K2, DUAL_12V⇆3V3_1BIT1:12V_TO_3V3_1BIT1:K3: HF41F-12-H
DUAL_12V⇆3V3_1BIT1:3V3_TO_12_1BIT1:U1: BTS442E2; TO170P440X1000X1975-5B
LED0, LED1, LED2: LED3MM
X0, X1: SWTCH_BLCK; 1751248

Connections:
3V3_TO_12_1BIT1:D$2: 3V3_TO_12_1BIT1:D3.A, 3V3_TO_12_1BIT1:D4.A
3V3_TO_12_1BIT1:N$1: 3V3_TO_12_1BIT1:D3.C, 3V3_TO_12_1BIT1:K2.1, 3V3_TO_12_1BIT1:U1.5
12V_TO_3V3_1BIT1:D$3: 12V_TO_3V3_1BIT1:D5.A, 12V_TO_3V3_1BIT1:D6.A
+3V3: 12V_TO_3V3_1BIT1:K3.4, BBB_IO1:C1.1, BBB_IO1:C2.A, BBB_IO1:IC1.9, BBB_IO1:IC1.18, BBB_IO1:R1.A, BBB_IO1:R2.A, BBB_IO1:SV1.1, DUAL_12V⇆3V3_1BIT1:12V_TO_3V3_1BIT1:K3.4
+12V: 3V3_TO_12_1BIT1:K2.4, 3V3_TO_12_1BIT1:U1.3, 12V_PWR_BLK:C1.1, 12V_PWR_BLK:PWR.2, DUAL_12V⇆3V3_1BIT1:3V3_TO_12_1BIT1:K2.4, DUAL_12V⇆3V3_1BIT1:3V3_TO_12_1BIT1:U1.3, X0.2, X1.2
BBB_IO1:SCL: BBB_IO1:IC1.12, BBB_IO1:R1.C, BBB_IO1:SV1.3
BBB_IO1:SDA: BBB_IO1:IC1.13, BBB_IO1:R2.C, BBB_IO1:SV1.4
DUAL_12V⇆3V3_1BIT1:3V3_TO_12_1BIT1:D$2: DUAL_12V⇆3V3_1BIT1:3V3_TO_12_1BIT1:D3.A, DUAL_12V⇆3V3_1BIT1:3V3_TO_12_1BIT1:D4.A
DUAL_12V⇆3V3_1BIT1:3V3_TO_12_1BIT1:N$1: DUAL_12V⇆3V3_1BIT1:3V3_TO_12_1BIT1:D3.C, DUAL_12V⇆3V3_1BIT1:3V3_TO_12_1BIT1:K2.1, DUAL_12V⇆3V3_1BIT1:3V3_TO_12_1BIT1:U1.5
DUAL_12V⇆3V3_1BIT1:12V_TO_3V3_1BIT1:D$3: DUAL_12V⇆3V3_1BIT1:12V_TO_3V3_1BIT1:D5.A, DUAL_12V⇆3V3_1BIT1:12V_TO_3V3_1BIT1:D6.A
GND: 3V3_TO_12_1BIT1:D4.C, 3V3_TO_12_1BIT1:K2.2, 12V_PWR_BLK:C1.2, 12V_PWR_BLK:PWR.1, 12V_TO_3V3_1BIT1:D6.C, 12V_TO_3V3_1BIT1:K3.2, DUAL_12V⇆3V3_1BIT1:3V3_TO_12_1BIT1:D4.C, DUAL_12V⇆3V3_1BIT1:3V3_TO_12_1BIT1:K2.2, DUAL_12V⇆3V3_1BIT1:12V_TO_3V3_1BIT1:D6.C, DUAL_12V⇆3V3_1BIT1:12V_TO_3V3_1BIT1:K3.2, LED0.K, LED1.K, LED2.K
GND3: 3V3_TO_12_1BIT1:U1.1, BBB_IO1:C1.2, BBB_IO1:C2.C, BBB_IO1:IC1.10, BBB_IO1:IC1.15, BBB_IO1:IC1.16, BBB_IO1:IC1.17, BBB_IO1:R3.C, BBB_IO1:R4.C, BBB_IO1:SV1.2, DUAL_12V⇆3V3_1BIT1:3V3_TO_12_1BIT1:U1.1
unnamed: 3V3_TO_12_1BIT1:K2.5, LED1.A
unnamed: 12V_TO_3V3_1BIT1:D5.C, 12V_TO_3V3_1BIT1:K3.1, LED0.A, X0.1
unnamed: DUAL_12V⇆3V3_1BIT1:3V3_TO_12_1BIT1:K2.5, DUAL_12V⇆3V3_1BIT1:12V_TO_3V3_1BIT1:D5.C, DUAL_12V⇆3V3_1BIT1:12V_TO_3V3_1BIT1:K3.1, LED2.A, X1.1
unnamed: BBB_IO1:IC1.8, DUAL_12V⇆3V3_1BIT1:3V3_TO_12_1BIT1:U1.2
unnamed: BBB_IO1:IC1.1, BBB_IO1:R4.A, DUAL_12V⇆3V3_1BIT1:12V_TO_3V3_1BIT1:K3.5
unnamed: 3V3_TO_12_1BIT1:U1.2, BBB_IO1:IC1.28
unnamed: 12V_TO_3V3_1BIT1:K3.5, BBB_IO1:IC1.21, BBB_IO1:R3.A
